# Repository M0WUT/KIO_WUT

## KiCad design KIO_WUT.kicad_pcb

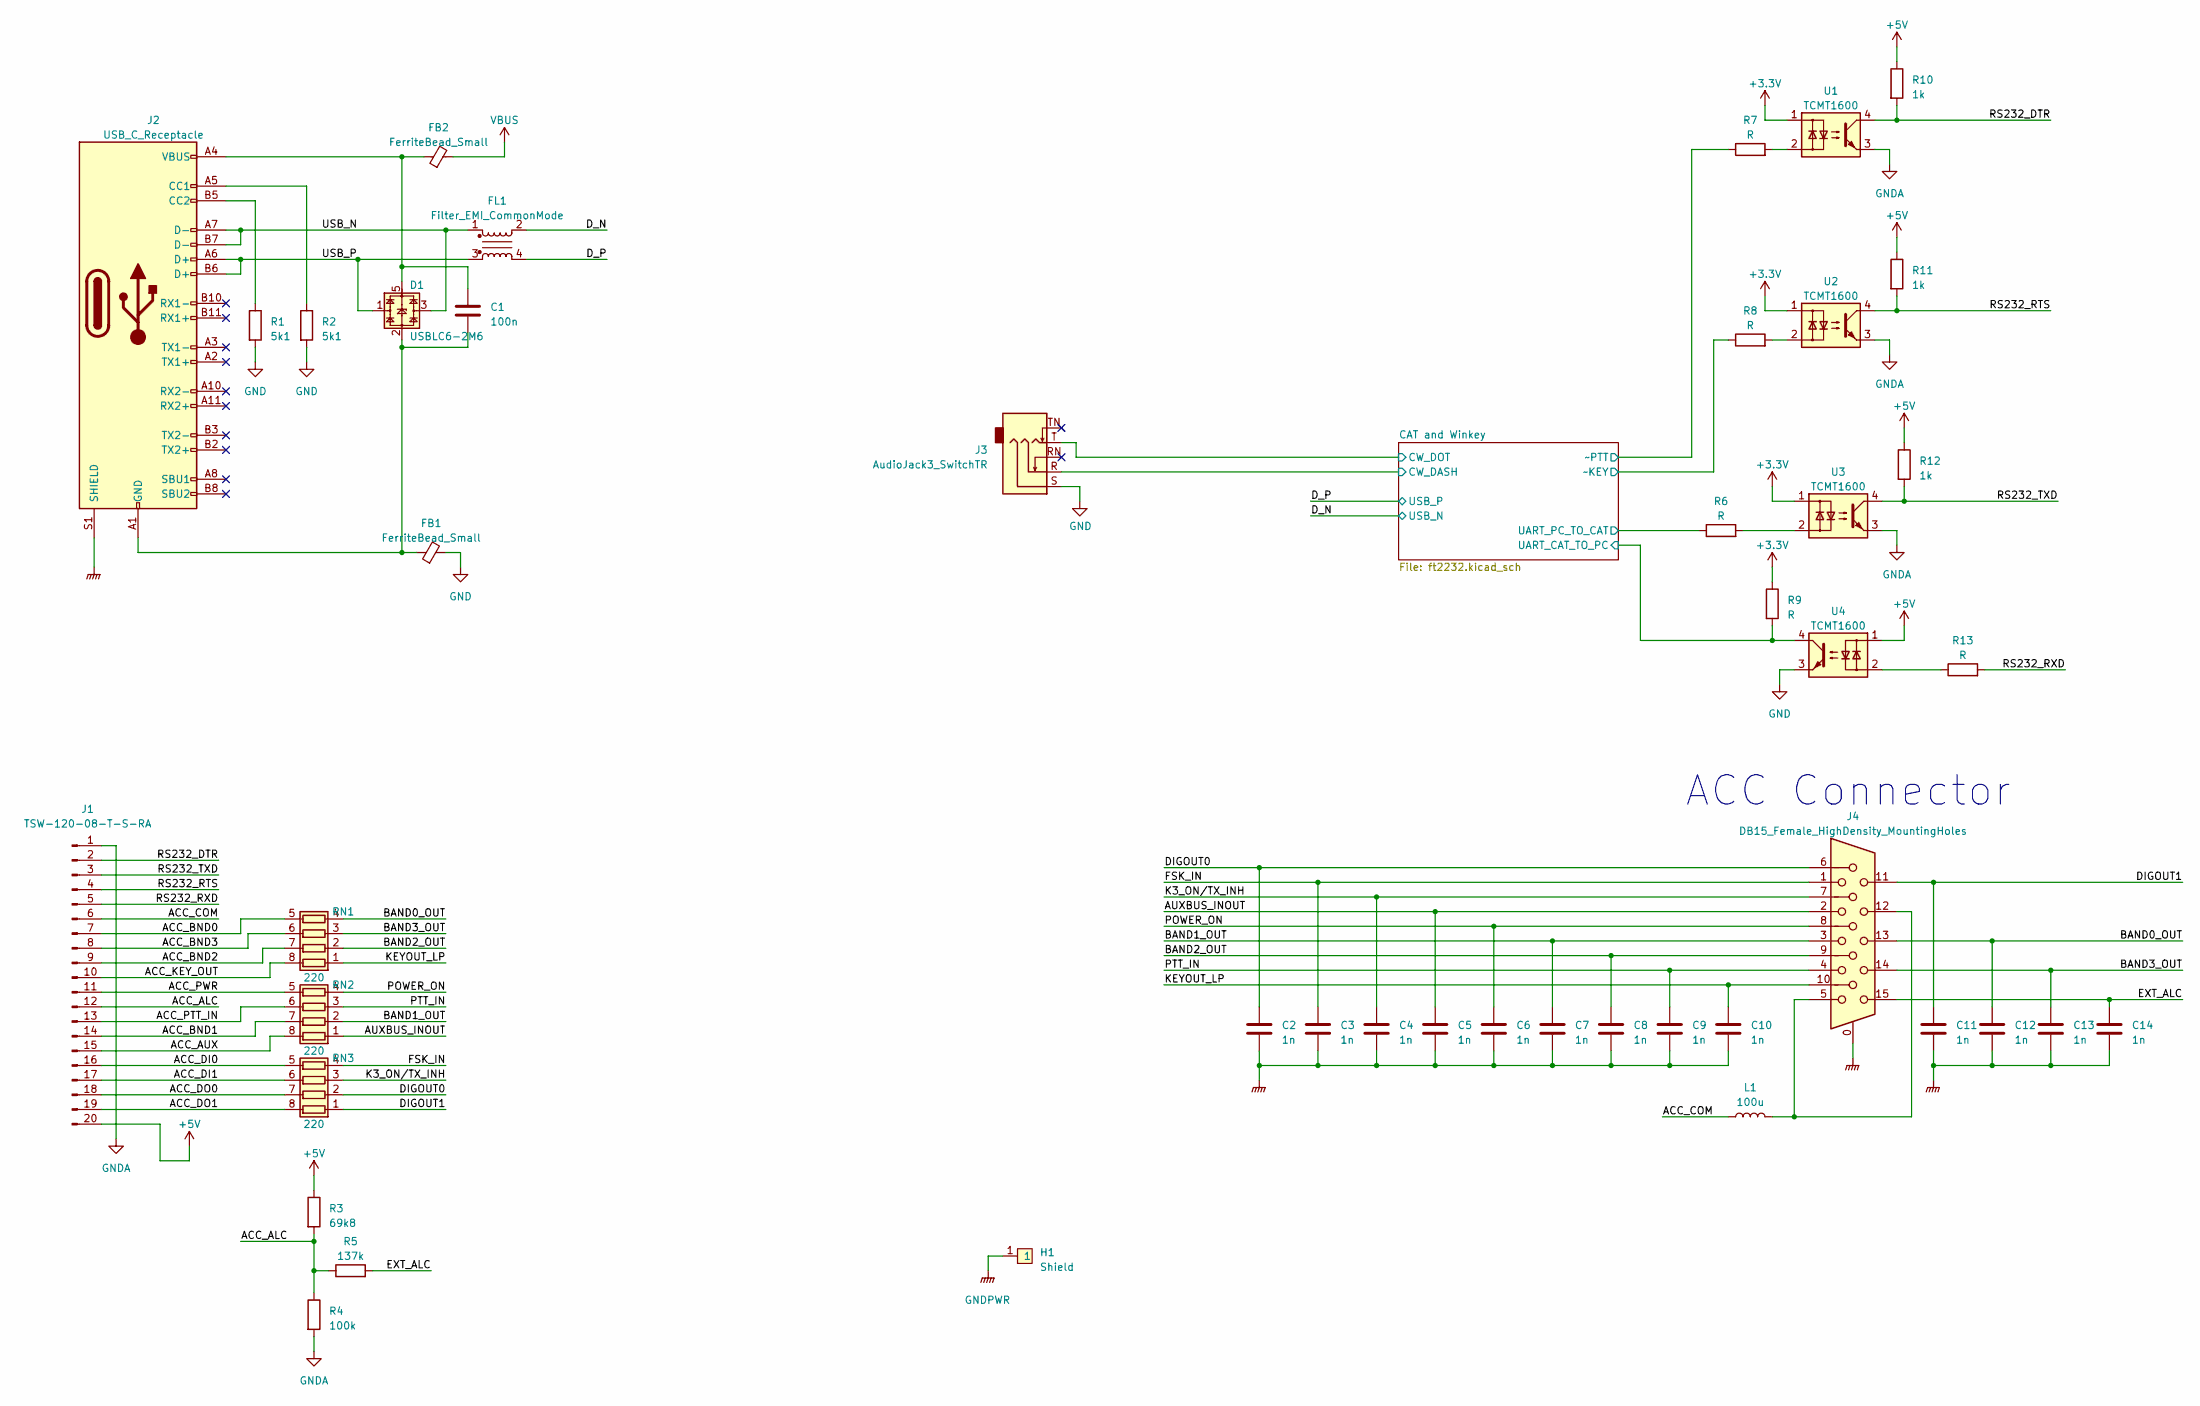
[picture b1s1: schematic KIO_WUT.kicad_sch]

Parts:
C1: 100n; C_0402_1005Metric
C2, C3, C4, C5, C6, C7, C8, C9, C10, C11, C12, C13, C14: 1n; C_0402_1005Metric
D1: USBLC6-2M6; TVS_ST_USBLC6-2M6
FB1, FB2: FerriteBead_Small; L_0603_1608Metric
FL1: Filter_EMI_CommonMode; Wurth_CM_USB_744231091
H1: Shield; Shield_Masach_MS737-10_73.4x27.8x3mm_TH
J1: TSW-120-08-T-S-RA; PinHeader_1x20_P2.54mm_Horizontal
J2: USB_C_Receptacle; USB-C_Amphenol_MUSBR-M1C1-M0
J3: AudioJack3_SwitchTR; Jack_3.5mm_CUI_SJ1-3535NG-GR_Horizontal_CircularHoles_Green
J4: DB15_Female_HighDensity_MountingHoles; D-Sub_HD15_TE_2311763-2_RA
L1: 100u; L_1210_3225Metric
R1, R2: 5k1; R_0402_1005Metric
R3: 69k8; R_0402_1005Metric
R4: 100k; R_0402_1005Metric
R5: 137k; R_0402_1005Metric
R6, R7, R8, R9, R13: R; R_0402_1005Metric
R10, R11, R12: 1k; R_0402_1005Metric
RN1, RN2, RN3: 220; R_Cat16-4
U1, U2, U3, U4: TCMT1600; SOP-4_4.4x2.6mm_P1.27mm

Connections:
+3V3: R9.1, U1.1, U2.1, U3.1; also elsewhere on the board
+5V: J1.20, R3.1, R10.1, R11.1, R12.1, U4.1; also elsewhere on the board
/ACC_ALC: J1.12, R3.2, R4.1, R5.1
/ACC_AUX: J1.15, RN2.8 (R1.2)
/ACC_BND0: J1.7, RN1.5 (R4.2)
/ACC_BND1: J1.14, RN2.7 (R2.2)
/ACC_BND2: J1.9, RN1.7 (R2.2)
/ACC_BND3: J1.8, RN1.6 (R3.2)
/ACC_COM: J1.6, L1.1
/ACC_DI0: J1.16, RN3.5 (R4.2)
/ACC_DI1: J1.17, RN3.6 (R3.2)
/ACC_DO0: J1.18, RN3.7 (R2.2)
/ACC_DO1: J1.19, RN3.8 (R1.2)
/ACC_KEY_OUT: J1.10, RN1.8 (R1.2)
/ACC_PTT_IN: J1.13, RN2.6 (R3.2)
/ACC_PWR: J1.11, RN2.5 (R4.2)
/AUXBUS_INOUT: C5.1, J4.2, RN2.1 (R1.1)
/BAND0_OUT: C12.1, J4.13, RN1.4 (R4.1)
/BAND1_OUT: C7.1, J4.3, RN2.2 (R2.1)
/BAND2_OUT: C8.1, J4.9, RN1.2 (R2.1)
/BAND3_OUT: C13.1, J4.14, RN1.3 (R3.1)
/CAT and Winkey/CW_DASH: J3.R; also elsewhere on the board
/CAT and Winkey/CW_DOT: J3.T; also elsewhere on the board
/CAT and Winkey/UART_CAT_TO_PC: R9.2, U4.4; also elsewhere on the board
/CAT and Winkey/UART_PC_TO_CAT: R6.1; also elsewhere on the board
/CAT and Winkey/~KEY: R8.1; also elsewhere on the board
/CAT and Winkey/~PTT: R7.1; also elsewhere on the board
/DIGOUT0: C2.1, J4.6, RN3.2 (R2.1)
/DIGOUT1: C11.1, J4.11, RN3.1 (R1.1)
/D_N: FL1.2; also elsewhere on the board
/D_P: FL1.4; also elsewhere on the board
/EXT_ALC: C14.1, J4.15, R5.2
/FSK_IN: C3.1, J4.1, RN3.4 (R4.1)
/K3_ON/TX_INH: C4.1, J4.7, RN3.3 (R3.1)
/KEYOUT_LP: C10.1, J4.10, RN1.1 (R1.1)
/POWER_ON: C6.1, J4.8, RN2.4 (R4.1)
/PTT_IN: C9.1, J4.4, RN2.3 (R3.1)
/RS232_DTR: J1.2, R10.2, U1.4
/RS232_RTS: J1.4, R11.2, U2.4
/RS232_RXD: J1.5, R13.2
/RS232_TXD: J1.3, R12.2, U3.4
/USB_N: D1.3, D1.4, FL1.1, J2.A7 (D-), J2.B7 (D-)
/USB_P: D1.1, D1.6, FL1.3, J2.A6 (D+), J2.B6 (D+)
GND: FB1.2, J3.S, R1.2, R2.2, U4.3; also elsewhere on the board
GNDA: J1.1, R4.2, U1.3, U2.3, U3.3
GNDPWR: C2.2, C3.2, C4.2, C5.2, C6.2, C7.2, C8.2, C9.2, C10.2, C11.2, C12.2, C13.2, C14.2, H1.1, J2.S1 (SHIELD), J4.0
unnamed: C1.1, D1.5, FB2.1, J2.A4 (VBUS), J2.A9 (VBUS), J2.B4 (VBUS), J2.B9 (VBUS)
unnamed: C1.2, D1.2, FB1.1, J2.A1 (GND), J2.A12 (GND), J2.B1 (GND), J2.B12 (GND)
unnamed: J2.A5 (CC1), R2.1
unnamed: J2.B5 (CC2), R1.1
unnamed: J4.5, J4.12, L1.2
unnamed: R6.2, U3.2
unnamed: R7.2, U1.2
unnamed: R8.2, U2.2
unnamed: R13.1, U4.2
VBUS: FB2.2

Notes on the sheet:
ACC Connector

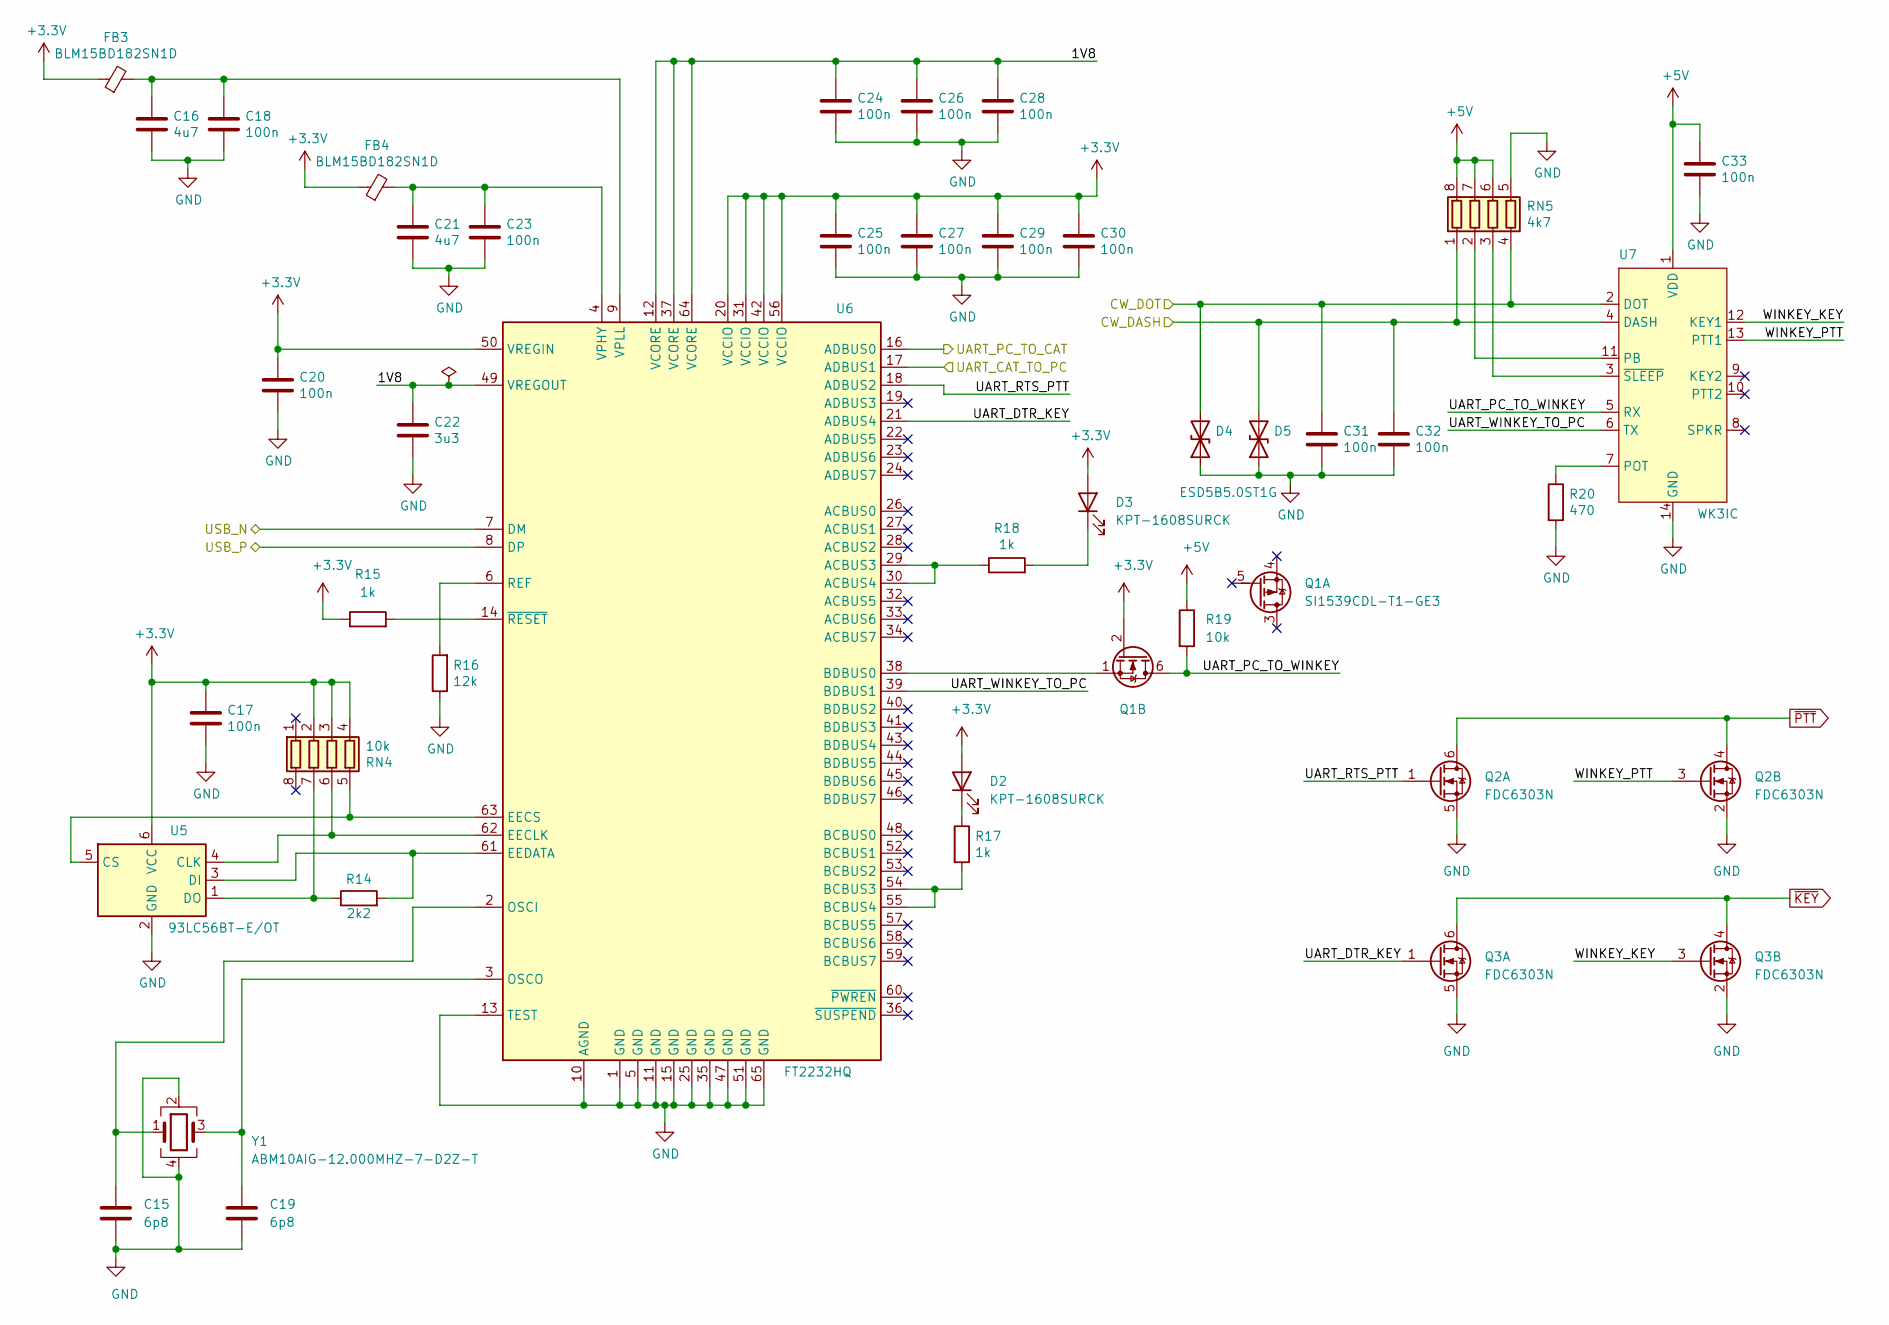
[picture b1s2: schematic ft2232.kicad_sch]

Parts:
C15, C19: 6p8; C_0402_1005Metric
C16, C21: 4u7; C_0402_1005Metric
C17, C18, C20, C23, C24, C25, C26, C27, C28, C29, C30, C31, C32, C33: 100n; C_0402_1005Metric
C22: 3u3; C_0402_1005Metric
D2, D3: KPT-1608SURCK; LED_0603_1608Metric
D4, D5: ESD5B5.0ST1G; D_SOD-523
FB3, FB4: BLM15BD182SN1D; L_0402_1005Metric
Q1: SI1539CDL-T1-GE3; SOT-363_SC-70-6
Q2, Q3: FDC6303N; SOT-23-6
R14: 2k2; R_0402_1005Metric
R15, R17, R18: 1k; R_0402_1005Metric
R16: 12k; R_0402_1005Metric
R19: 10k; R_0402_1005Metric
R20: 470; R_0402_1005Metric
RN4: 10k; R_Cat16-4
RN5: 4k7; R_Cat16-4
U5: 93LC56BT-E/OT; SOT-23-6
U6: FT2232HQ; QFN-64-1EP_9x9mm_P0.5mm_EP4.35x4.35mm
U7: WK3IC; SOIC-14_3.9x8.7mm_P1.27mm
Y1: ABM10AIG-12.000MHZ-7-D2Z-T; Crystal_SMD_2520-4Pin_2.5x2.0mm

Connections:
+3V3: C17.1, C20.1, C25.1, C27.1, C29.1, C30.1, D2.2 (A), D3.2 (A), FB3.1, FB4.1, Q1.2, R15.1, RN4.2 (R2.1), RN4.3 (R3.1), RN4.4 (R4.1), U5.6 (VCC), U6.20 (VCCIO), U6.31 (VCCIO), U6.42 (VCCIO), U6.50 (VREGIN), U6.56 (VCCIO); also elsewhere on the board
+5V: C33.1, R19.1, RN5.6 (R3.2), RN5.7 (R2.2), RN5.8 (R1.2), U7.1 (VDD); also elsewhere on the board
/CAT and Winkey/1V8: C22.1, C24.1, C26.1, C28.1, U6.12 (VCORE), U6.37 (VCORE), U6.49 (VREGOUT), U6.64 (VCORE)
/CAT and Winkey/CW_DASH: C32.1, D5.2 (A2), RN5.1 (R1.1), U7.4 (DASH); also elsewhere on the board
/CAT and Winkey/CW_DOT: C31.1, D4.2 (A2), RN5.4 (R4.1), U7.2 (DOT); also elsewhere on the board
/CAT and Winkey/UART_CAT_TO_PC: U6.17 (ADBUS1); also elsewhere on the board
/CAT and Winkey/UART_DTR_KEY: Q3.1 (G), U6.21 (ADBUS4)
/CAT and Winkey/UART_PC_TO_CAT: U6.16 (ADBUS0); also elsewhere on the board
/CAT and Winkey/UART_PC_TO_WINKEY: Q1.6, R19.2, U7.5 (RX)
/CAT and Winkey/UART_RTS_PTT: Q2.1 (G), U6.18 (ADBUS2)
/CAT and Winkey/UART_WINKEY_TO_PC: U6.39 (BDBUS1), U7.6 (TX)
/CAT and Winkey/WINKEY_KEY: Q3.3 (G), U7.12 (KEY1)
/CAT and Winkey/WINKEY_PTT: Q2.3 (G), U7.13 (PTT1)
/CAT and Winkey/~KEY: Q3.4 (D), Q3.6 (D); also elsewhere on the board
/CAT and Winkey/~PTT: Q2.4 (D), Q2.6 (D); also elsewhere on the board
/D_N: U6.7 (DM); also elsewhere on the board
/D_P: U6.8 (DP); also elsewhere on the board
GND: C15.2, C16.2, C17.2, C18.2, C19.2, C20.2, C21.2, C22.2, C23.2, C24.2, C25.2, C26.2, C27.2, C28.2, C29.2, C30.2, C31.2, C32.2, C33.2, D4.1 (A1), D5.1 (A1), Q2.2 (S), Q2.5 (S), Q3.2 (S), Q3.5 (S), R16.1, R20.2, RN5.5 (R4.2), U5.2 (GND), U6.1 (GND), U6.5 (GND), U6.10 (AGND), U6.11 (GND), U6.13 (TEST), U6.15 (GND), U6.25 (GND), U6.35 (GND), U6.47 (GND), U6.51 (GND), U6.65 (GND), U7.14 (GND), Y1.2, Y1.4; also elsewhere on the board
unnamed: C15.1, U6.2 (OSCI), Y1.1
unnamed: C16.1, C18.1, FB3.2, U6.9 (VPLL)
unnamed: C19.1, U6.3 (OSCO), Y1.3
unnamed: C21.1, C23.1, FB4.2, U6.4 (VPHY)
unnamed: D2.1 (K), R17.1
unnamed: D3.1 (K), R18.2
unnamed: Q1.1, U6.38 (BDBUS0)
unnamed: R14.1, RN4.7 (R2.2), U5.1 (DO)
unnamed: R14.2, U5.3 (DI), U6.61 (EEDATA)
unnamed: R15.2, U6.14 (~RESET)
unnamed: R16.2, U6.6 (REF)
unnamed: R17.2, U6.54 (BCBUS3), U6.55 (BCBUS4)
unnamed: R18.1, U6.29 (ACBUS3), U6.30 (ACBUS4)
unnamed: R20.1, U7.7 (POT)
unnamed: RN4.5 (R4.2), U5.5 (CS), U6.63 (EECS)
unnamed: RN4.6 (R3.2), U5.4 (CLK), U6.62 (EECLK)
unnamed: RN5.2 (R2.1), U7.11 (PB)
unnamed: RN5.3 (R3.1), U7.3 (~SLEEP)

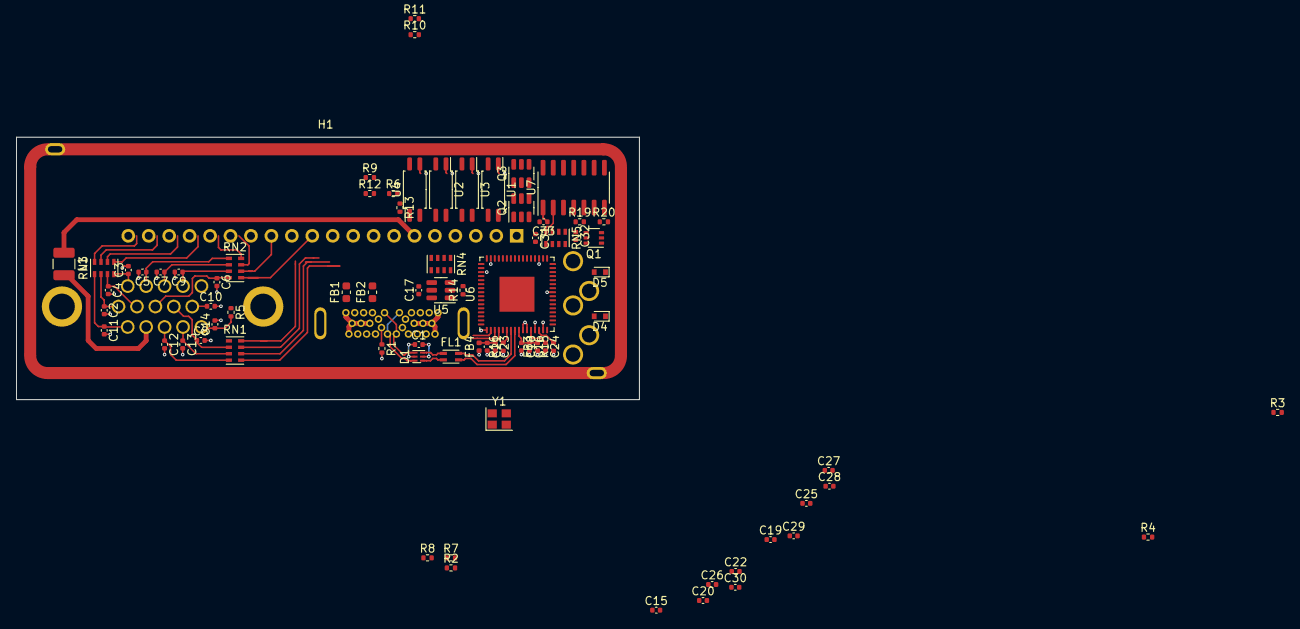
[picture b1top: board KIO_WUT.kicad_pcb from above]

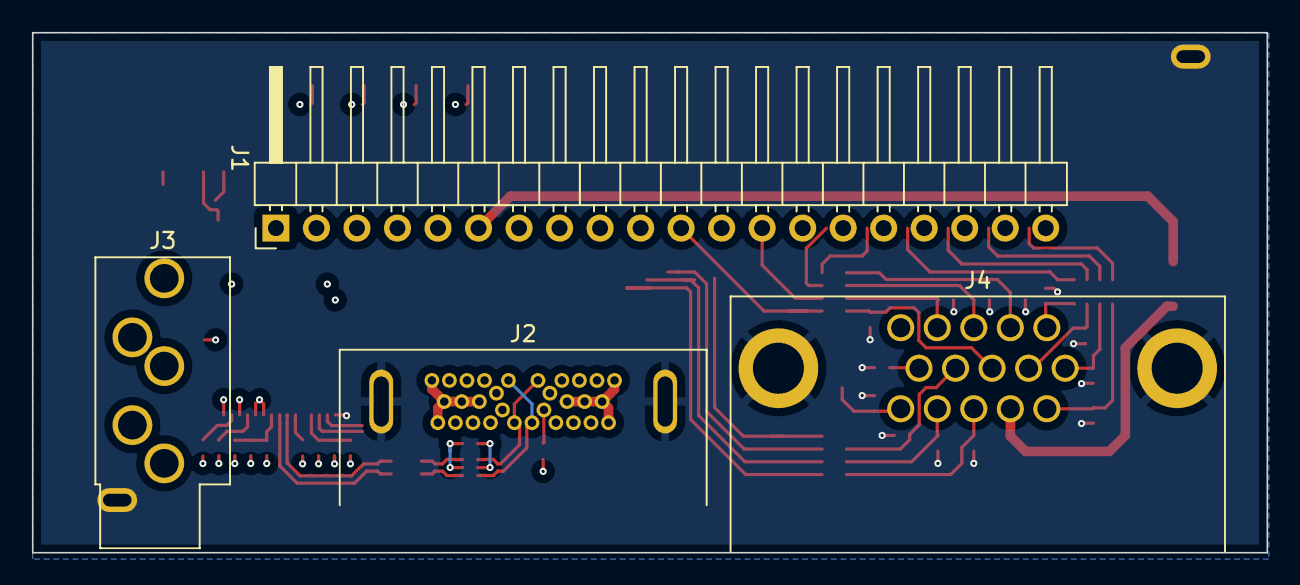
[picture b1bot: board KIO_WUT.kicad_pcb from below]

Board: 4 copper layers, 77.4 x 32.6 mm, 81 parts (4 on the bottom side), 76 nets.

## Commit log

2018-10-08 added ft2232
2018-10-18 added eeprom and expanded sch
2018-10-31 Resized PCB now I have reference board
2018-11-04 finished input side of usb isolator
2018-11-05 most of usb hub implemented
2018-11-11 mirrored digital section of board to allow for easier routing to io
2018-11-27 finally got the decoupling caps for the db15 to fit
2018-11-29 reorganised decoupling caps to be slightly less crazy
2018-12-01 fixed some silkscreen issues
2018-12-01 added missing pullups to band lines
2018-12-02 complete apart from sound card and PIC
2018-12-12 destruction in the name of progress...
2019-01-07 nearly there...
2019-01-24 Initial changes from v1 + started code
2019-01-27 Started work but fighting Microchip's stupid library
2019-01-28 it lives!!!
2019-01-29 All 4 UARTS TXing
2019-01-29 removed stuff leftover from debugging
2019-01-31 loopback tests working
2019-01-31 updated gitignore to (hopefully) remove junk
2019-01-31 messing with git ignore
2019-01-31 Removed all of the junk files
2019-02-01 All the forwarding between devices working :)
2019-02-02 all done, now for testing with K3
2019-02-13 Implementing Board changes from v1
2019-02-18 v2 pcb ordered
2019-02-18 Update with a change that I wish was in v2
2019-03-07 renumbered parts, minor BOM update
2019-03-14 minor code fixes
2021-06-12 testing branching worked as planned
2021-06-12 Added kicad project
2021-06-14 more layout work
